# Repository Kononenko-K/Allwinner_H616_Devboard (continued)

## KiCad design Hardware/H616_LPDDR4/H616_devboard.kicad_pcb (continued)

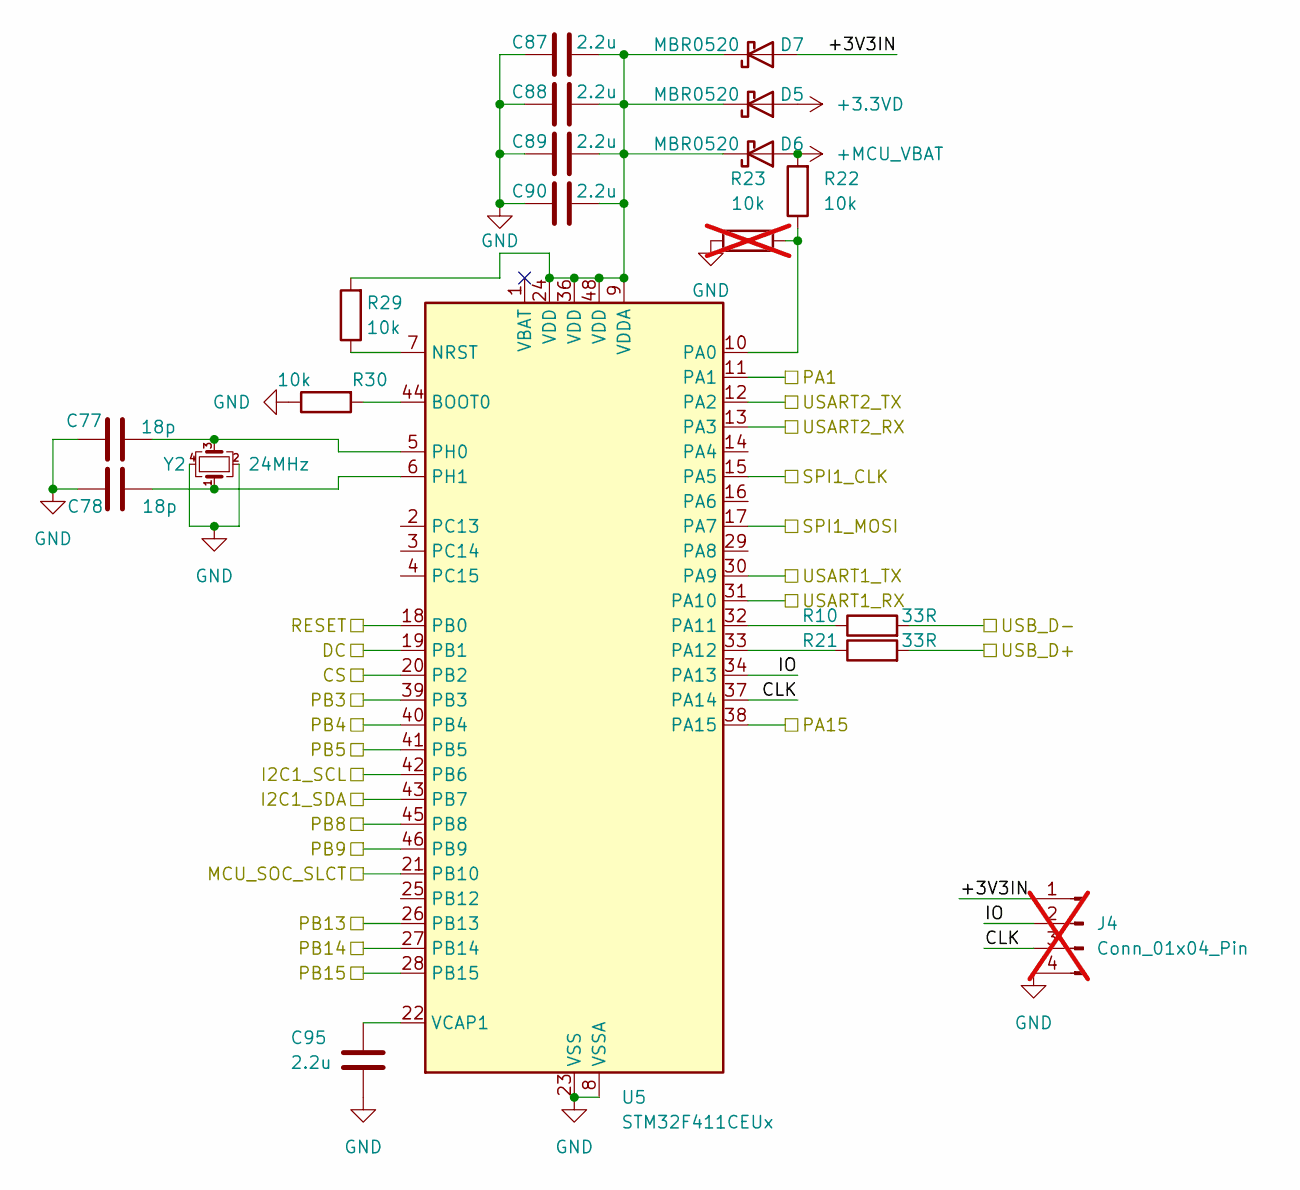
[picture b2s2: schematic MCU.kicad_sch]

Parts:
C77, C78: 18p; C_0402_1005Metric_Pad0.74x0.62mm_HandSolder; Part Number 0402CG180J500NT
C87, C88, C89, C90, C95: 2.2u; C_0402_1005Metric_Pad0.74x0.62mm_HandSolder; Part Number CL05A225KO5NQNC
D5, D6, D7: MBR0520; D_SOD-123; Part Number MBR0520
J4: Conn_01x04_Pin; PinHeader_1x04_P2.54mm_Vertical; not fitted
R10, R21: 33R; R_0402_1005Metric_Pad0.72x0.64mm_HandSolder; Part Number RC0402FR-0733RL
R22, R29, R30: 10k; R_0402_1005Metric_Pad0.72x0.64mm_HandSolder; Part Number RC0402FR-0710KL
R23: 10k; R_0402_1005Metric_Pad0.72x0.64mm_HandSolder; not fitted
U5: STM32F411CEUx; QFN-48-1EP_7x7mm_P0.5mm_EP5.6x5.6mm; Part Number STM32F411CEU6
Y2: 24MHz; Crystal_SMD_2520-4Pin_2.5x2.0mm; Part Number XTM25024000JT00351001

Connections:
+3.3VD: D5.2 (A); also elsewhere on the board
+MCU_VBAT: D6.2 (A), R22.2; also elsewhere on the board
/32R_SW: U5.28 (PB15); also elsewhere on the board
/AGC_SW: U5.27 (PB14); also elsewhere on the board
/CENTER_KEY: U5.40 (PB4); also elsewhere on the board
/IO1/DBG_RX2: U5.12 (PA2); also elsewhere on the board
/IO1/DBG_TX2: U5.13 (PA3); also elsewhere on the board
/IO1/UART5_RX: U5.30 (PA9); also elsewhere on the board
/IO1/UART5_TX: U5.31 (PA10); also elsewhere on the board
/LEFT_KEY: U5.39 (PB3); also elsewhere on the board
/MCU/+3V3IN: D7.2 (A), J4.1
/MCU/CLK: J4.3, U5.37 (PA14)
/MCU/CS: U5.20 (PB2); also elsewhere on the board
/MCU/DC: U5.19 (PB1); also elsewhere on the board
/MCU/I2C1_SCL: U5.42 (PB6); also elsewhere on the board
/MCU/I2C1_SDA: U5.43 (PB7); also elsewhere on the board
/MCU/IO: J4.2, U5.34 (PA13)
/MCU/MCU_SOC_SLCT: U5.21 (PB10); also elsewhere on the board
/MCU/PB8: U5.45 (PB8); also elsewhere on the board
/MCU/PB9: U5.46 (PB9); also elsewhere on the board
/MCU/RESET: U5.18 (PB0); also elsewhere on the board
/MCU/SPI1_CLK: U5.15 (PA5); also elsewhere on the board
/MCU/SPI1_MOSI: U5.17 (PA7); also elsewhere on the board
/MCU_D+: R21.2; also elsewhere on the board
/MCU_D-: R10.2; also elsewhere on the board
/N_CHRG: U5.11 (PA1); also elsewhere on the board
/POWER_KEY: U5.41 (PB5); also elsewhere on the board
/PSU_SW: U5.26 (PB13); also elsewhere on the board
/RIGHT_KEY: U5.38 (PA15); also elsewhere on the board
GND: C77.1, C78.1, C87.1, C88.1, C89.1, C90.1, C95.1, J4.4, R23.1, R30.1, U5.8 (VSSA), U5.23 (VSS), U5.35 (VSS), U5.47 (VSS), U5.49 (VSS), Y2.2, Y2.4; also elsewhere on the board
unnamed: C87.2, C88.2, C89.2, C90.2, D5.1 (K), D6.1 (K), D7.1 (K), R29.2, U5.9 (VDDA), U5.24 (VDD), U5.36 (VDD), U5.48 (VDD)
unnamed: R30.2, U5.44 (BOOT0)
unnamed: R29.1, U5.7 (NRST)
unnamed: R22.1, R23.2, U5.10 (PA0)
unnamed: R10.1, U5.32 (PA11)
unnamed: R21.1, U5.33 (PA12)
unnamed: C77.2, U5.5 (PH0), Y2.3
unnamed: C78.2, U5.6 (PH1), Y2.1
unnamed: C95.2, U5.22 (VCAP1)

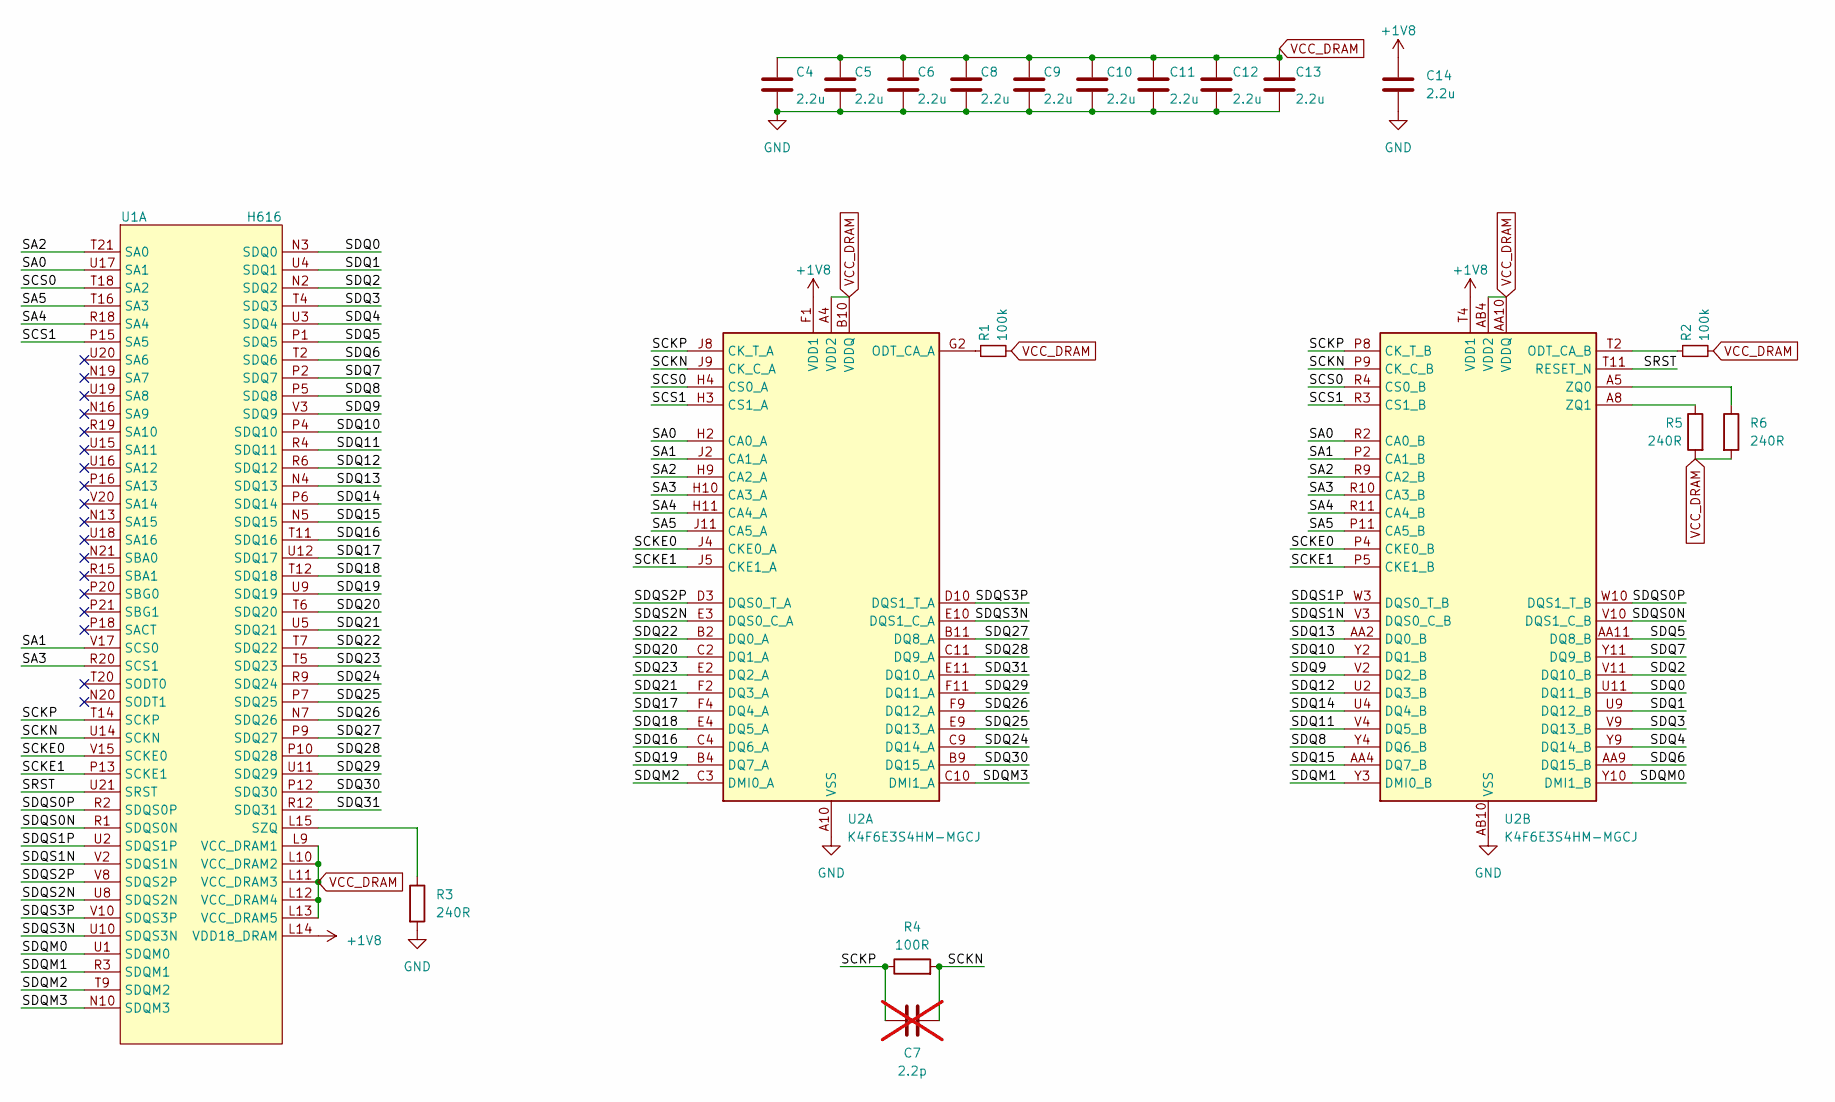
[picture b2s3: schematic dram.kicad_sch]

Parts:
C4, C5, C6, C8, C9, C10, C11, C12, C13, C14: 2.2u; C_0402_1005Metric_Pad0.74x0.62mm_HandSolder; Part Number CL05A225KO5NQNC
C7: 2.2p; C_0402_1005Metric_Pad0.74x0.62mm_HandSolder; not fitted
R1, R2: 100k; R_0402_1005Metric_Pad0.72x0.64mm_HandSolder; Part Number RC0402FR-07100KL
R3, R5, R6: 240R; R_0402_1005Metric_Pad0.72x0.64mm_HandSolder; Part Number RC0402FR-07240RL
R4: 100R; R_0402_1005Metric_Pad0.72x0.64mm_HandSolder; Part Number RC0402FR-07100RL
U1: H616; H616_TFBGA284; Part Number H616
U2: IS43LQ32256A-062BLI; BGA-200_10.0x14.5mm_Layout12x22_P0.80x0.65mm; Part Number K4F6E3S4HM-MGCJ

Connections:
+1V8: C14.1, U1.L14 (VDD18_DRAM), U2.F1 (VDD1), U2.F12 (VDD1), U2.G4 (VDD1), U2.G9 (VDD1), U2.T4 (VDD1), U2.T9 (VDD1), U2.U1 (VDD1), U2.U12 (VDD1); also elsewhere on the board
/DRAM/SA0: U1.U17 (SA1), U2.H2 (CA0_A), U2.R2 (CA0_B)
/DRAM/SA1: U1.V17 (SCS0), U2.J2 (CA1_A), U2.P2 (CA1_B)
/DRAM/SA2: U1.T21 (SA0), U2.H9 (CA2_A), U2.R9 (CA2_B)
/DRAM/SA3: U1.R20 (SCS1), U2.H10 (CA3_A), U2.R10 (CA3_B)
/DRAM/SA4: U1.R18 (SA4), U2.H11 (CA4_A), U2.R11 (CA4_B)
/DRAM/SA5: U1.T16 (SA3), U2.J11 (CA5_A), U2.P11 (CA5_B)
/DRAM/SCKE0: U1.V15 (SCKE0), U2.J4 (CKE0_A), U2.P4 (CKE0_B)
/DRAM/SCKE1: U1.P13 (SCKE1), U2.J5 (CKE1_A), U2.P5 (CKE1_B)
/DRAM/SCKN: C7.2, R4.2, U1.U14 (SCKN), U2.J9 (CK_C_A), U2.P9 (CK_C_B)
/DRAM/SCKP: C7.1, R4.1, U1.T14 (SCKP), U2.J8 (CK_T_A), U2.P8 (CK_T_B)
/DRAM/SCS0: U1.T18 (SA2), U2.H4 (CS0_A), U2.R4 (CS0_B)
/DRAM/SCS1: U1.P15 (SA5), U2.H3 (CS1_A), U2.R3 (CS1_B)
/DRAM/SDQ0: U1.N3 (SDQ0), U2.U11 (DQ11_B)
/DRAM/SDQ1: U1.U4 (SDQ1), U2.U9 (DQ12_B)
/DRAM/SDQ2: U1.N2 (SDQ2), U2.V11 (DQ10_B)
/DRAM/SDQ3: U1.T4 (SDQ3), U2.V9 (DQ13_B)
/DRAM/SDQ4: U1.U3 (SDQ4), U2.Y9 (DQ14_B)
/DRAM/SDQ5: U1.P1 (SDQ5), U2.AA11 (DQ8_B)
/DRAM/SDQ6: U1.T2 (SDQ6), U2.AA9 (DQ15_B)
/DRAM/SDQ7: U1.P2 (SDQ7), U2.Y11 (DQ9_B)
/DRAM/SDQ8: U1.P5 (SDQ8), U2.Y4 (DQ6_B)
/DRAM/SDQ9: U1.V3 (SDQ9), U2.V2 (DQ2_B)
/DRAM/SDQ10: U1.P4 (SDQ10), U2.Y2 (DQ1_B)
/DRAM/SDQ11: U1.R4 (SDQ11), U2.V4 (DQ5_B)
/DRAM/SDQ12: U1.R6 (SDQ12), U2.U2 (DQ3_B)
/DRAM/SDQ13: U1.N4 (SDQ13), U2.AA2 (DQ0_B)
/DRAM/SDQ14: U1.P6 (SDQ14), U2.U4 (DQ4_B)
/DRAM/SDQ15: U1.N5 (SDQ15), U2.AA4 (DQ7_B)
/DRAM/SDQ16: U1.T11 (SDQ16), U2.C4 (DQ6_A)
/DRAM/SDQ17: U1.U12 (SDQ17), U2.F4 (DQ4_A)
/DRAM/SDQ18: U1.T12 (SDQ18), U2.E4 (DQ5_A)
/DRAM/SDQ19: U1.U9 (SDQ19), U2.B4 (DQ7_A)
/DRAM/SDQ20: U1.T6 (SDQ20), U2.C2 (DQ1_A)
/DRAM/SDQ21: U1.U5 (SDQ21), U2.F2 (DQ3_A)
/DRAM/SDQ22: U1.T7 (SDQ22), U2.B2 (DQ0_A)
/DRAM/SDQ23: U1.T5 (SDQ23), U2.E2 (DQ2_A)
/DRAM/SDQ24: U1.R9 (SDQ24), U2.C9 (DQ14_A)
/DRAM/SDQ25: U1.P7 (SDQ25), U2.E9 (DQ13_A)
/DRAM/SDQ26: U1.N7 (SDQ26), U2.F9 (DQ12_A)
/DRAM/SDQ27: U1.P9 (SDQ27), U2.B11 (DQ8_A)
/DRAM/SDQ28: U1.P10 (SDQ28), U2.C11 (DQ9_A)
/DRAM/SDQ29: U1.U11 (SDQ29), U2.F11 (DQ11_A)
/DRAM/SDQ30: U1.P12 (SDQ30), U2.B9 (DQ15_A)
/DRAM/SDQ31: U1.R12 (SDQ31), U2.E11 (DQ10_A)
/DRAM/SDQM0: U1.U1 (SDQM0), U2.Y10 (DMI1_B)
/DRAM/SDQM1: U1.R3 (SDQM1), U2.Y3 (DMI0_B)
/DRAM/SDQM2: U1.T9 (SDQM2), U2.C3 (DMI0_A)
/DRAM/SDQM3: U1.N10 (SDQM3), U2.C10 (DMI1_A)
/DRAM/SDQS0N: U1.R1 (SDQS0N), U2.V10 (DQS1_C_B)
/DRAM/SDQS0P: U1.R2 (SDQS0P), U2.W10 (DQS1_T_B)
/DRAM/SDQS1N: U1.V2 (SDQS1N), U2.V3 (DQS0_C_B)
/DRAM/SDQS1P: U1.U2 (SDQS1P), U2.W3 (DQS0_T_B)
/DRAM/SDQS2N: U1.U8 (SDQS2N), U2.E3 (DQS0_C_A)
/DRAM/SDQS2P: U1.V8 (SDQS2P), U2.D3 (DQS0_T_A)
/DRAM/SDQS3N: U1.U10 (SDQS3N), U2.E10 (DQS1_C_A)
/DRAM/SDQS3P: U1.V10 (SDQS3P), U2.D10 (DQS1_T_A)
/DRAM/SRST: U1.U21 (SRST), U2.T11 (RESET_N)
GND: C4.2, C5.2, C6.2, C8.2, C9.2, C10.2, C11.2, C12.2, C13.2, C14.2, R3.2, U2.A3 (VSS), U2.A10 (VSS), U2.AB3 (VSS), U2.AB5 (VSS), U2.AB8 (VSS), U2.AB10 (VSS), U2.C1 (VSS), U2.C5 (VSS), U2.C8 (VSS), U2.C12 (VSS), U2.D2 (VSS), U2.D4 (VSS), U2.D9 (VSS), U2.D11 (VSS), U2.E1 (VSS), U2.E5 (VSS), U2.E8 (VSS), U2.E12 (VSS), U2.G1 (VSS), U2.G3 (VSS), U2.G5 (VSS), U2.G8 (VSS), U2.G10 (VSS), U2.G12 (VSS), U2.J1 (VSS), U2.J3 (VSS), U2.J10 (VSS), U2.J12 (VSS), U2.K2 (VSS), U2.K4 (VSS), U2.K9 (VSS), U2.K11 (VSS), U2.N2 (VSS), U2.N4 (VSS), U2.N9 (VSS), U2.N11 (VSS), U2.P1 (VSS), U2.P3 (VSS), U2.P10 (VSS), U2.P12 (VSS), U2.T1 (VSS), U2.T3 (VSS), U2.T5 (VSS), U2.T8 (VSS), U2.T10 (VSS), U2.T12 (VSS), U2.V1 (VSS), U2.V5 (VSS), U2.V8 (VSS), U2.V12 (VSS), U2.W2 (VSS), U2.W4 (VSS), U2.W9 (VSS), U2.W11 (VSS), U2.Y1 (VSS), U2.Y5 (VSS), U2.Y8 (VSS), U2.Y12 (VSS); also elsewhere on the board
unnamed: R3.1, U1.L15 (SZQ)
unnamed: R1.1, U2.G2 (ODT_CA_A)
unnamed: R2.1, U2.T2 (ODT_CA_B)
unnamed: R6.1, U2.A5 (ZQ0)
unnamed: R5.1, U2.A8 (ZQ1)
VCC_DRAM: C4.1, C5.1, C6.1, C8.1, C9.1, C10.1, C11.1, C12.1, C13.1, R1.2, R2.2, R5.2, R6.2, U1.L9 (VCC_DRAM1), U1.L10 (VCC_DRAM2), U1.L11 (VCC_DRAM3), U1.L12 (VCC_DRAM4), U1.L13 (VCC_DRAM5), U2.A4 (VDD2), U2.A9 (VDD2), U2.AA3 (VDDQ), U2.AA5 (VDDQ), U2.AA8 (VDDQ), U2.AA10 (VDDQ), U2.AB4 (VDD2), U2.AB9 (VDD2), U2.B3 (VDDQ), U2.B5 (VDDQ), U2.B8 (VDDQ), U2.B10 (VDDQ), U2.D1 (VDDQ), U2.D5 (VDDQ), U2.D8 (VDDQ), U2.D12 (VDDQ), U2.F3 (VDDQ), U2.F5 (VDD2), U2.F8 (VDD2), U2.F10 (VDDQ), U2.H1 (VDD2), U2.H5 (VDD2), U2.H8 (VDD2), U2.H12 (VDD2), U2.K1 (VDD2), U2.K3 (VDD2), U2.K10 (VDD2), U2.K12 (VDD2), U2.N1 (VDD2), U2.N3 (VDD2), U2.N10 (VDD2), U2.N12 (VDD2), U2.R1 (VDD2), U2.R5 (VDD2), U2.R8 (VDD2), U2.R12 (VDD2), U2.U3 (VDDQ), U2.U5 (VDD2), U2.U8 (VDD2), U2.U10 (VDDQ), U2.W1 (VDDQ), U2.W5 (VDDQ), U2.W8 (VDDQ), U2.W12 (VDDQ); also elsewhere on the board

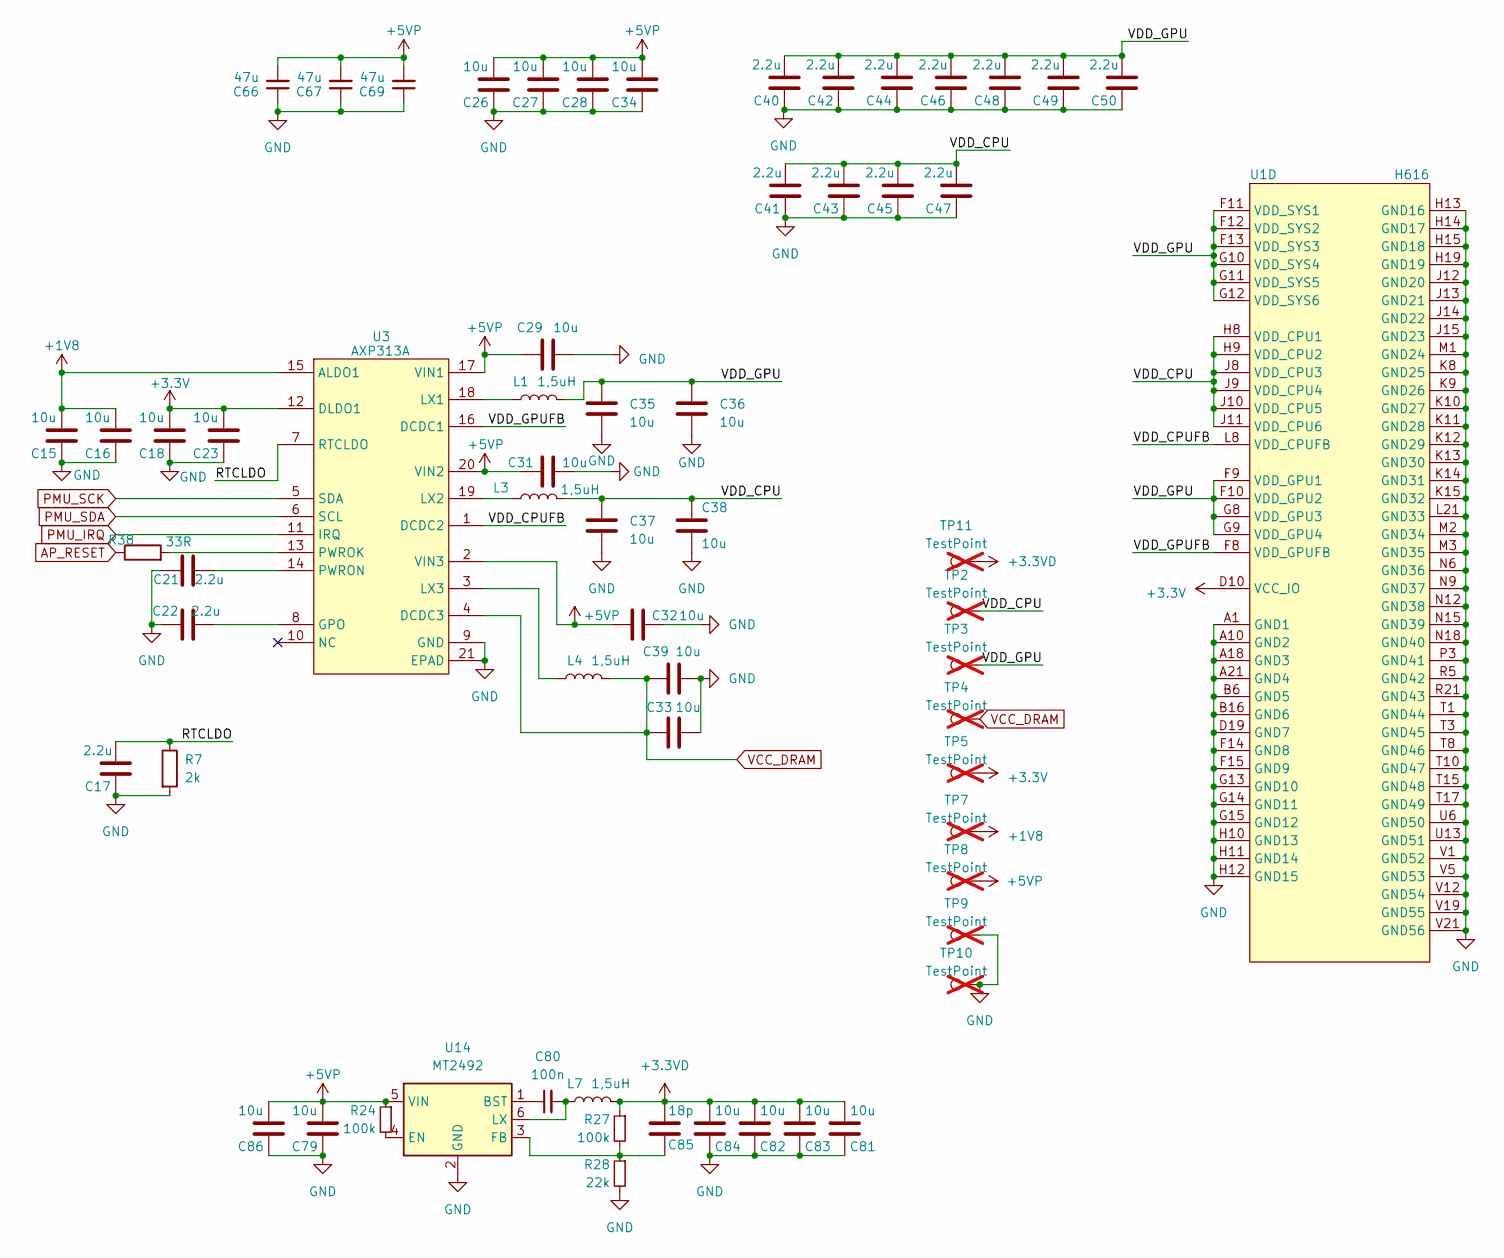
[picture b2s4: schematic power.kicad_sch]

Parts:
C15, C16, C18, C23, C26, C27, C28, C29, C31, C32, C33, C34, C35, C36, C37, C38, C39, C79, C81, C82, C83, C84, C86: 10u; C_0402_1005Metric_Pad0.74x0.62mm_HandSolder; Part Number GRM155R61A106ME44D
C17, C21, C22, C40, C41, C42, C43, C44, C45, C46, C47, C48, C49, C50: 2.2u; C_0402_1005Metric_Pad0.74x0.62mm_HandSolder; Part Number CL05A225KO5NQNC
C66, C67, C69: 47u; C_1210_3225Metric_Pad1.33x2.70mm_HandSolder; Part Number CS3225X7R476K160NRL
C80: 100n; C_0402_1005Metric_Pad0.74x0.62mm_HandSolder; Part Number CL05B104KO5NNNC
C85: 18p; C_0402_1005Metric_Pad0.74x0.62mm_HandSolder; Part Number 0402CG180J500NT
L1, L3, L4, L7: 1,5uH; L_Changjiang_FNR252010S; Part Number FTC252012S2R2MBCA
R7: 2k; R_0402_1005Metric_Pad0.72x0.64mm_HandSolder; Part Number RC0402FR-072KL
R24, R27: 100k; R_0402_1005Metric_Pad0.72x0.64mm_HandSolder; Part Number RC0402FR-07100KL
R28: 22k; R_0402_1005Metric_Pad0.72x0.64mm_HandSolder; Part Number RC0402FR-0722KL
R38: 33R; R_0402_1005Metric_Pad0.72x0.64mm_HandSolder; Part Number RC0402FR-0733RL
TP2, TP3, TP4, TP5, TP7, TP8, TP9, TP10, TP11: TestPoint; TestPoint_THTPad_D1.0mm_Drill0.5mm; not fitted
U1: H616; H616_TFBGA284; Part Number H616
U3: QFN-20-1EP_3x3mm_P0.4mm_EP1.65x1.65mm_ThermalVias; Part Number AXP313A
U14: MT2492; SOT-23-6; Part Number MT2492

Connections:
+1V8: C15.2, C16.2, TP7.1, U3.15 (ALDO1); also elsewhere on the board
+3.3V: C18.2, C23.2, TP5.1, U1.D10 (VCC_IO), U3.12 (DLDO1); also elsewhere on the board
+3.3VD: C81.2, C82.2, C83.2, C84.2, C85.2, L7.2, R27.1, TP11.1; also elsewhere on the board
+5VP: C26.2, C27.2, C28.2, C29.1, C31.1, C32.1, C34.2, C66.2, C67.2, C69.2, C79.2, C86.2, R24.1, TP8.1, U3.2 (VIN3), U3.17 (VIN1), U3.20 (VIN2), U14.5 (VIN); also elsewhere on the board
/POWER/RTCLDO: C17.2, R7.1, U3.7 (RTCLDO)
/POWER/VDD_CPU: C37.1, C38.2, C41.2, C43.2, C45.2, C47.2, L3.2, TP2.1, U1.H8 (VDD_CPU1), U1.H9 (VDD_CPU2), U1.J8 (VDD_CPU3), U1.J9 (VDD_CPU4), U1.J10 (VDD_CPU5), U1.J11 (VDD_CPU6)
/POWER/VDD_CPUFB: U1.L8 (VDD_CPUFB), U3.1 (DCDC2)
/POWER/VDD_GPU: C35.1, C36.1, C40.2, C42.2, C44.2, C46.2, C48.2, C49.2, C50.2, L1.2, TP3.1, U1.F9 (VDD_GPU1), U1.F10 (VDD_GPU2), U1.F11 (VDD_SYS1), U1.F12 (VDD_SYS2), U1.F13 (VDD_SYS3), U1.G8 (VDD_GPU3), U1.G9 (VDD_GPU4), U1.G10 (VDD_SYS4), U1.G11 (VDD_SYS5), U1.G12 (VDD_SYS6)
/POWER/VDD_GPUFB: U1.F8 (VDD_GPUFB), U3.16 (DCDC1)
AP_RESET: R38.1; also elsewhere on the board
GND: C15.1, C16.1, C17.1, C18.1, C21.1, C22.1, C23.1, C26.1, C27.1, C28.1, C29.2, C31.2, C32.2, C33.2, C34.1, C35.2, C36.2, C37.2, C38.1, C39.2, C40.1, C41.1, C42.1, C43.1, C44.1, C45.1, C46.1, C47.1, C48.1, C49.1, C50.1, C66.1, C67.1, C69.1, C79.1, C81.1, C82.1, C83.1, C84.1, C86.1, R7.2, R28.2, TP9.1, TP10.1, U1.A1 (GND1), U1.A10 (GND2), U1.A18 (GND3), U1.A21 (GND4), U1.B6 (GND5), U1.B16 (GND6), U1.D19 (GND7), U1.F14 (GND8), U1.F15 (GND9), U1.G13 (GND10), U1.G14 (GND11), U1.G15 (GND12), U1.H10 (GND13), U1.H11 (GND14), U1.H12 (GND15), U1.H13 (GND16), U1.H14 (GND17), U1.H15 (GND18), U1.H19 (GND19), U1.J12 (GND20), U1.J13 (GND21), U1.J14 (GND22), U1.J15 (GND23), U1.K8 (GND25), U1.K9 (GND26), U1.K10 (GND27), U1.K11 (GND28), U1.K12 (GND29), U1.K13 (GND30), U1.K14 (GND31), U1.K15 (GND32), U1.L21 (GND33), U1.M1 (GND24), U1.M2 (GND34), U1.M3 (GND35), U1.N6 (GND36), U1.N9 (GND37), U1.N12 (GND38), U1.N15 (GND39), U1.N18 (GND40), U1.P3 (GND41), U1.R5 (GND42), U1.R21 (GND43), U1.T1 (GND44), U1.T3 (GND45), U1.T8 (GND46), U1.T10 (GND47), U1.T15 (GND48), U1.T17 (GND49), U1.U6 (GND50), U1.U13 (GND51), U1.V1 (GND52), U1.V5 (GND53), U1.V12 (GND54), U1.V19 (GND55), U1.V21 (GND56), U3.9 (GND), U3.21 (EPAD), U14.2 (GND); also elsewhere on the board
unnamed: C22.2, U3.8 (GPO)
unnamed: L1.1, U3.18 (LX1)
unnamed: L3.1, U3.19 (LX2)
unnamed: L4.1, U3.3 (LX3)
unnamed: R38.2, U3.13 (PWROK)
unnamed: C21.2, U3.14 (PWRON)
unnamed: C80.1, U14.1 (BST)
unnamed: R24.2, U14.4 (EN)
unnamed: C85.1, R27.2, R28.1, U14.3 (FB)
unnamed: C80.2, L7.1, U14.6 (LX)
PMU_IRQ: U3.11 (IRQ); also elsewhere on the board
PMU_SCK: U3.5 (SDA); also elsewhere on the board
PMU_SDA: U3.6 (SCL); also elsewhere on the board
VCC_DRAM: C33.1, C39.1, L4.2, TP4.1, U3.4 (DCDC3); also elsewhere on the board

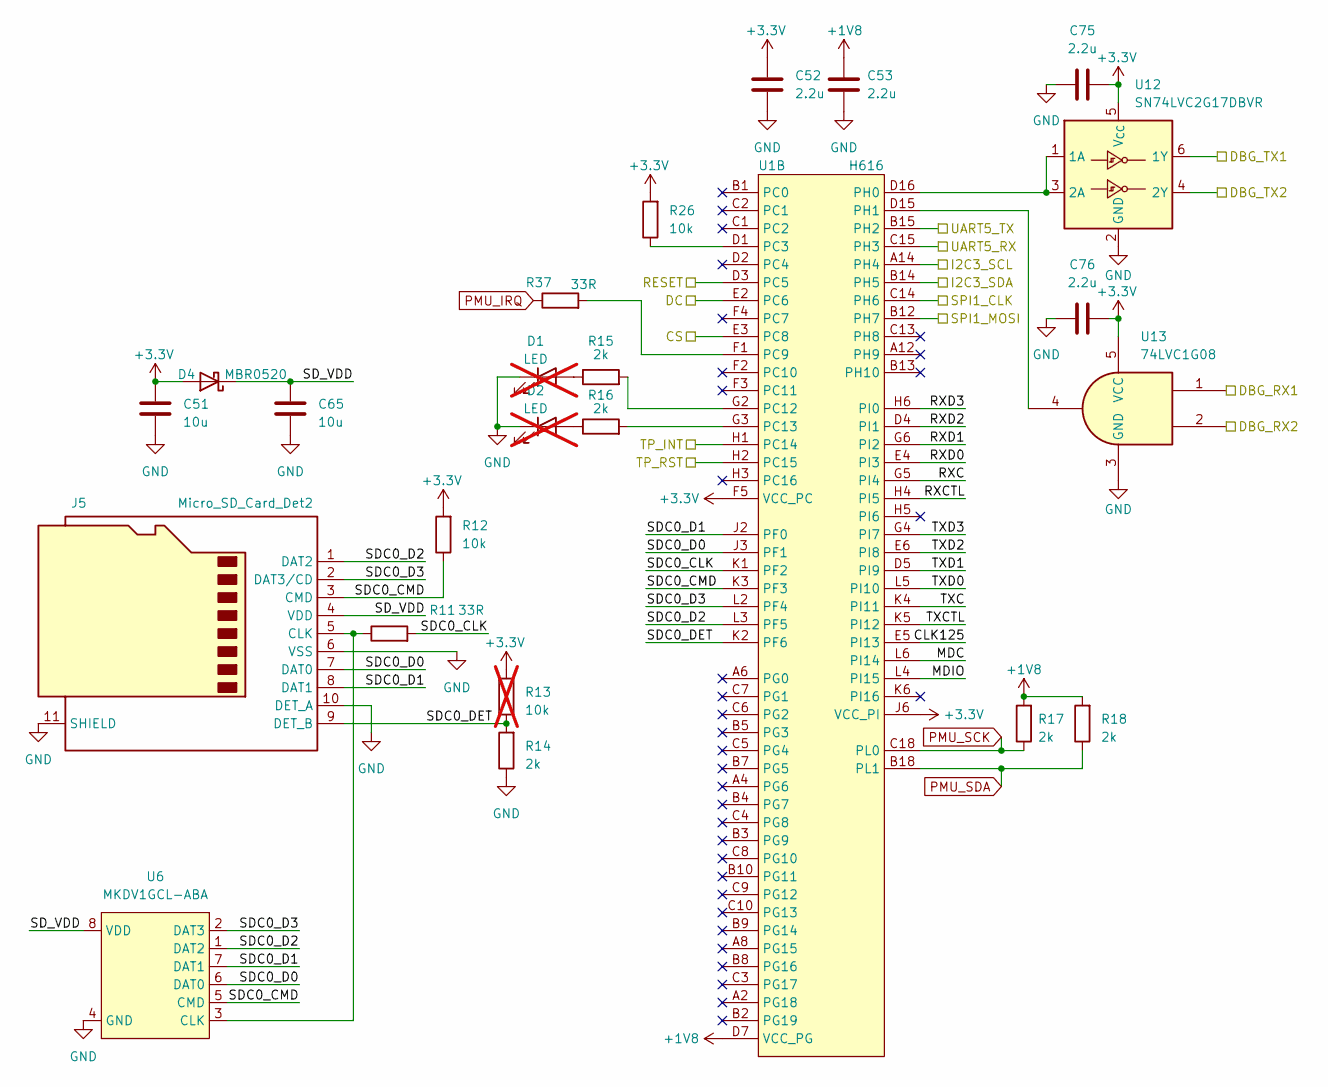
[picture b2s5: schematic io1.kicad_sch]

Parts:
C51, C65: 10u; C_0402_1005Metric_Pad0.74x0.62mm_HandSolder; Part Number GRM155R61A106ME44D
C52, C53, C75, C76: 2.2u; C_0402_1005Metric_Pad0.74x0.62mm_HandSolder; Part Number CL05A225KO5NQNC
D1, D2: LED; LED_0603_1608Metric_Pad1.05x0.95mm_HandSolder; not fitted
D4: MBR0520; D_SOD-123; Part Number MBR0520
J5: Micro_SD_Card_Det2; microSD_HC_Hirose_DM3AT-SF-PEJM5; Part Number HRS(Hirose)
R11, R37: 33R; R_0402_1005Metric_Pad0.72x0.64mm_HandSolder; Part Number RC0402FR-0733RL
R12, R26: 10k; R_0402_1005Metric_Pad0.72x0.64mm_HandSolder; Part Number RC0402FR-0710KL
R13: 10k; R_0402_1005Metric_Pad0.72x0.64mm_HandSolder; not fitted
R14, R15, R16, R17, R18: 2k; R_0402_1005Metric_Pad0.72x0.64mm_HandSolder; Part Number RC0402FR-072KL
U1: H616; H616_TFBGA284; Part Number H616
U6: MKDV1GCL-ABA; LGA-8_8x6mm_P1.27mm; Part Number MKDV08GCL-STP
U12: SN74LVC2G17DBVR; SOT-23-6; Part Number SN74LVC2G17DBVR(UMW)
U13: 74LVC1G08; SOT-23-5; Part Number 74LVC1G08GV

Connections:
+1V8: C53.1, R17.2, R18.2, U1.D7 (VCC_PG); also elsewhere on the board
+3.3V: C51.1, C52.1, C75.2, C76.2, D4.2 (A), R12.2, R13.2, R26.2, U1.F5 (VCC_PC), U1.J6 (VCC_PI), U12.5 (V_{CC}), U13.5 (VCC); also elsewhere on the board
/IO1/CLK125: U1.E5 (PI13)
/IO1/CS: U1.E3 (PC8); also elsewhere on the board
/IO1/DBG_RX1: U13.1; also elsewhere on the board
/IO1/DBG_RX2: U13.2; also elsewhere on the board
/IO1/DBG_TX1: U12.6 (1Y); also elsewhere on the board
/IO1/DBG_TX2: U12.4 (2Y); also elsewhere on the board
/IO1/DC: U1.E2 (PC6); also elsewhere on the board
/IO1/MDC: U1.L6 (PI14)
/IO1/MDIO: U1.L4 (PI15)
/IO1/RESET: U1.D3 (PC5); also elsewhere on the board
/IO1/RXC: U1.G5 (PI4)
/IO1/RXCTL: U1.H4 (PI5)
/IO1/RXD0: U1.E4 (PI3)
/IO1/RXD1: U1.G6 (PI2)
/IO1/RXD2: U1.D4 (PI1)
/IO1/RXD3: U1.H6 (PI0)
/IO1/SDC0_CLK: R11.2, U1.K1 (PF2)
/IO1/SDC0_CMD: J5.3 (CMD), R12.1, U1.K3 (PF3), U6.5 (CMD)
/IO1/SDC0_D0: J5.7 (DAT0), U1.J3 (PF1), U6.6 (DAT0)
/IO1/SDC0_D1: J5.8 (DAT1), U1.J2 (PF0), U6.7 (DAT1)
/IO1/SDC0_D2: J5.1 (DAT2), U1.L3 (PF5), U6.1 (DAT2)
/IO1/SDC0_D3: J5.2 (DAT3/CD), U1.L2 (PF4), U6.2 (DAT3)
/IO1/SDC0_DET: J5.9 (DET_B), R13.1, R14.2, U1.K2 (PF6)
/IO1/SD_VDD: C65.1, D4.1 (K), J5.4 (VDD), U6.8 (VDD)
/IO1/SPI1_CLK: U1.C14 (PH6); also elsewhere on the board
/IO1/SPI1_MOSI: U1.B12 (PH7); also elsewhere on the board
/IO1/TXC: U1.K4 (PI11)
/IO1/TXCTL: U1.K5 (PI12)
/IO1/TXD0: U1.L5 (PI10)
/IO1/TXD1: U1.D5 (PI9)
/IO1/TXD2: U1.E6 (PI8)
/IO1/TXD3: U1.G4 (PI7)
/IO1/UART5_RX: U1.C15 (PH3); also elsewhere on the board
/IO1/UART5_TX: U1.B15 (PH2); also elsewhere on the board
/TP_INT: U1.H1 (PC14); also elsewhere on the board
/TP_RST: U1.H2 (PC15); also elsewhere on the board
/TP_SCL: U1.A14 (PH4); also elsewhere on the board
/TP_SDA: U1.B14 (PH5); also elsewhere on the board
GND: C51.2, C52.2, C53.2, C65.2, C75.1, C76.1, D1.1 (K), D2.1 (K), J5.6 (VSS), J5.10 (DET_A), J5.11 (SHIELD), R14.1, U6.4 (GND), U12.2 (GND), U13.3 (GND); also elsewhere on the board
unnamed: D1.2 (A), R15.1
unnamed: D2.2 (A), R16.1
unnamed: J5.5 (CLK), R11.1, U6.3 (CLK)
unnamed: R26.1, U1.D1 (PC3)
unnamed: R37.2, U1.F1 (PC9)
unnamed: R15.2, U1.G2 (PC12)
unnamed: R16.2, U1.G3 (PC13)
unnamed: U1.D15 (PH1), U13.4
unnamed: U1.D16 (PH0), U12.1 (1A), U12.3 (2A)
PMU_IRQ: R37.1; also elsewhere on the board
PMU_SCK: R17.1, U1.C18 (PL0); also elsewhere on the board
PMU_SDA: R18.1, U1.B18 (PL1); also elsewhere on the board

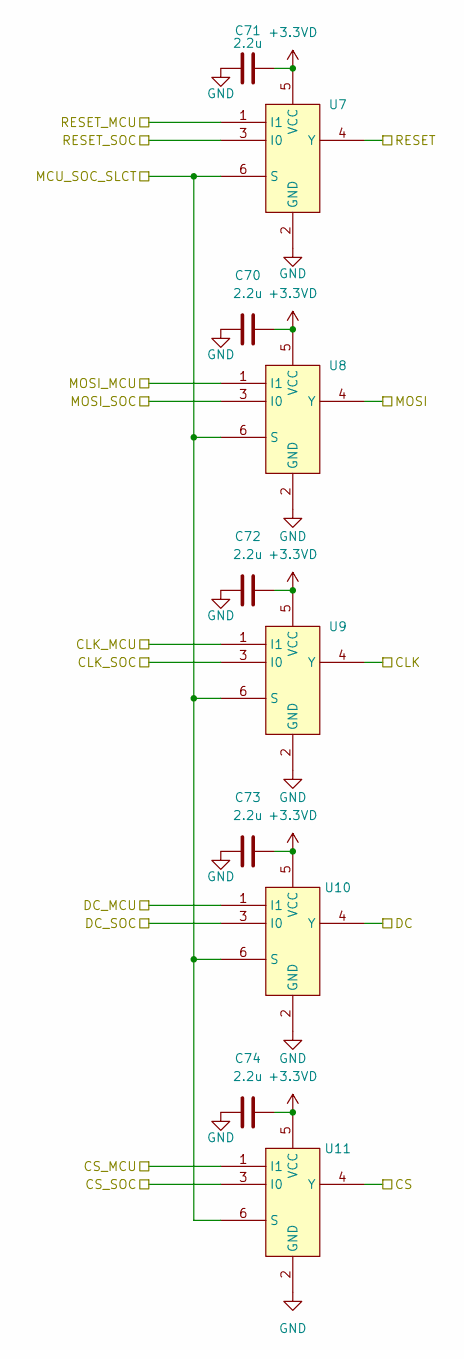
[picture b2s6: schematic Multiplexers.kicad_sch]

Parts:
C70, C71, C72, C73, C74: 2.2u; C_0402_1005Metric_Pad0.74x0.62mm_HandSolder; Part Number CL05A225KO5NQNC
U7, U8, U9, U10, U11: SOT-23-6; Part Number SN74LVC1G157DB(LX)

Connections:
+3.3VD: C70.2, C71.2, C72.2, C73.2, C74.2, U7.5 (VCC), U8.5 (VCC), U9.5 (VCC), U10.5 (VCC), U11.5 (VCC); also elsewhere on the board
/CLK: U9.4 (Y); also elsewhere on the board
/CS: U11.4 (Y); also elsewhere on the board
/DC: U10.4 (Y); also elsewhere on the board
/IO1/CS: U11.3 (I0); also elsewhere on the board
/IO1/DC: U10.3 (I0); also elsewhere on the board
/IO1/RESET: U7.3 (I0); also elsewhere on the board
/IO1/SPI1_CLK: U9.3 (I0); also elsewhere on the board
/IO1/SPI1_MOSI: U8.3 (I0); also elsewhere on the board
/MCU/CS: U11.1 (I1); also elsewhere on the board
/MCU/DC: U10.1 (I1); also elsewhere on the board
/MCU/MCU_SOC_SLCT: U7.6 (S), U8.6 (S), U9.6 (S), U10.6 (S), U11.6 (S); also elsewhere on the board
/MCU/RESET: U7.1 (I1); also elsewhere on the board
/MCU/SPI1_CLK: U9.1 (I1); also elsewhere on the board
/MCU/SPI1_MOSI: U8.1 (I1); also elsewhere on the board
/MOSI: U8.4 (Y); also elsewhere on the board
/RESET: U7.4 (Y); also elsewhere on the board
GND: C70.1, C71.1, C72.1, C73.1, C74.1, U7.2 (GND), U8.2 (GND), U9.2 (GND), U10.2 (GND), U11.2 (GND); also elsewhere on the board

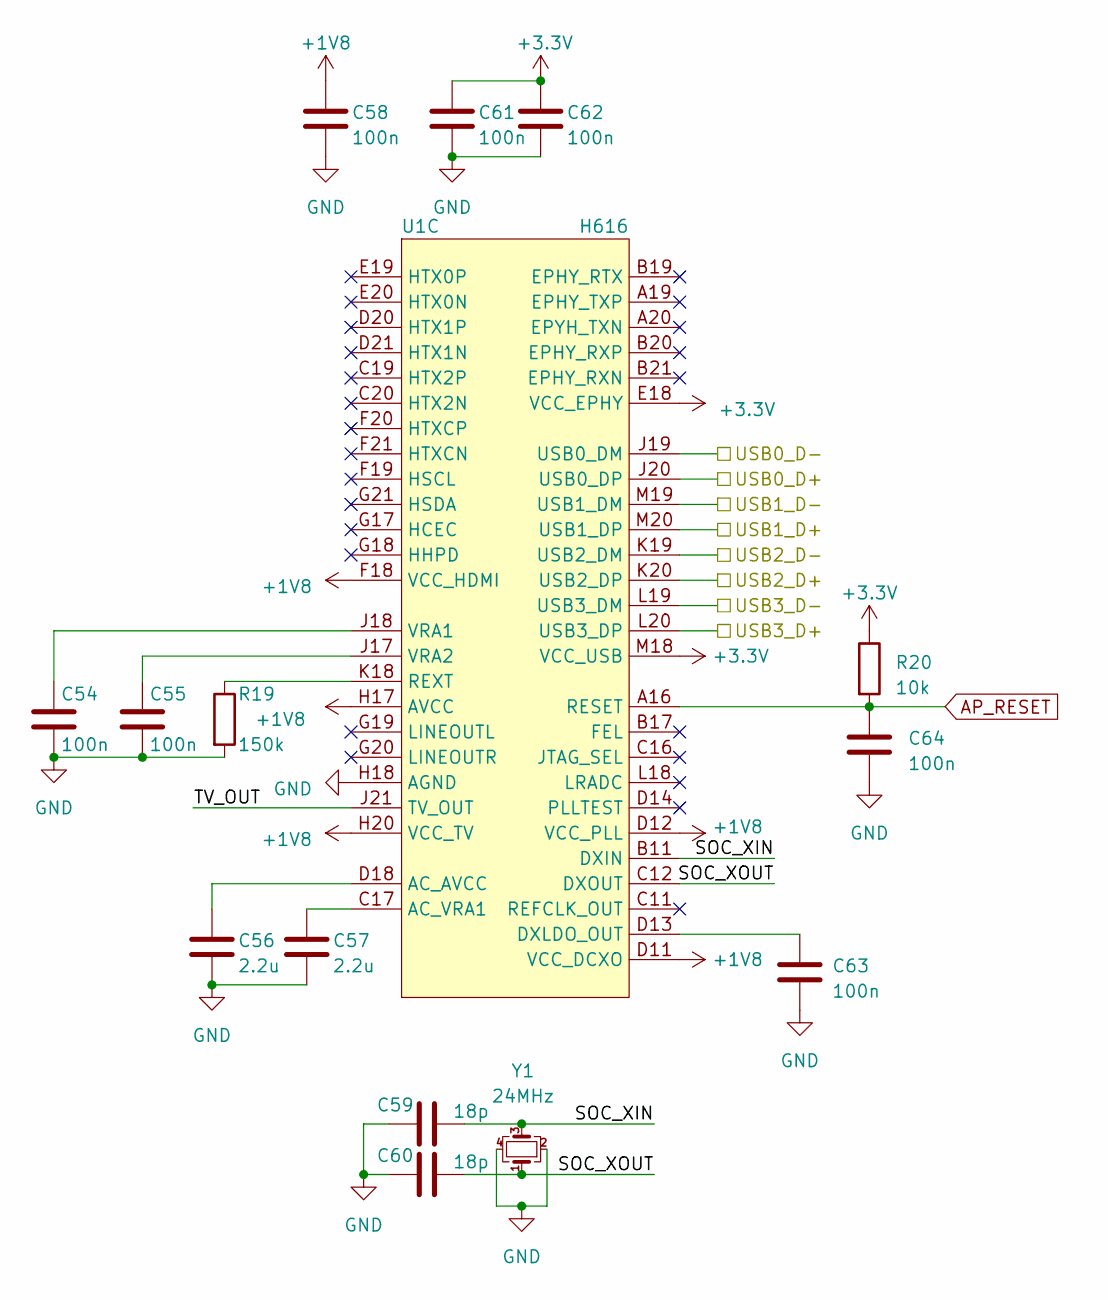
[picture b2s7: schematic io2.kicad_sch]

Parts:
C54, C55, C58, C61, C62, C63, C64: 100n; C_0402_1005Metric_Pad0.74x0.62mm_HandSolder; Part Number CL05B104KO5NNNC
C56, C57: 2.2u; C_0402_1005Metric_Pad0.74x0.62mm_HandSolder; Part Number CL05A225KO5NQNC
C59, C60: 18p; C_0402_1005Metric_Pad0.74x0.62mm_HandSolder; Part Number 0402CG180J500NT
R19: 150k; R_0402_1005Metric_Pad0.72x0.64mm_HandSolder; Part Number RC0402FR-07150KL
R20: 10k; R_0402_1005Metric_Pad0.72x0.64mm_HandSolder; Part Number RC0402FR-0710KL
U1: H616; H616_TFBGA284; Part Number H616
Y1: 24MHz; Crystal_SMD_2520-4Pin_2.5x2.0mm; Part Number XTM25024000JT00351001

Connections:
+1V8: C58.1, U1.D11 (VCC_DCXO), U1.D12 (VCC_PLL), U1.F18 (VCC_HDMI), U1.H17 (AVCC), U1.H20 (VCC_TV); also elsewhere on the board
+3.3V: C61.1, C62.1, R20.1, U1.E18 (VCC_EPHY), U1.M18 (VCC_USB); also elsewhere on the board
/AUX_D+: U1.J20 (USB0_DP); also elsewhere on the board
/AUX_D-: U1.J19 (USB0_DM); also elsewhere on the board
/CODEC_D+: U1.K20 (USB2_DP); also elsewhere on the board
/CODEC_D-: U1.K19 (USB2_DM); also elsewhere on the board
/IO2/SOC_XIN: C59.2, U1.B11 (DXIN), Y1.3
/IO2/SOC_XOUT: C60.2, U1.C12 (DXOUT), Y1.1
/IO2/TV_OUT: U1.J21 (TV_OUT)
/IO2/USB3_D+: U1.L20 (USB3_DP)
/IO2/USB3_D-: U1.L19 (USB3_DM)
/MCU_D+: U1.M20 (USB1_DP); also elsewhere on the board
/MCU_D-: U1.M19 (USB1_DM); also elsewhere on the board
AP_RESET: C64.1, R20.2, U1.A16 (RESET); also elsewhere on the board
GND: C54.2, C55.2, C56.2, C57.2, C58.2, C59.1, C60.1, C61.2, C62.2, C63.2, C64.2, R19.2, U1.H18 (AGND), Y1.2, Y1.4; also elsewhere on the board
unnamed: C56.1, U1.D18 (AC_AVCC)
unnamed: C57.1, U1.C17 (AC_VRA1)
unnamed: C63.1, U1.D13 (DXLDO_OUT)
unnamed: R19.1, U1.K18 (REXT)
unnamed: C54.1, U1.J18 (VRA1)
unnamed: C55.1, U1.J17 (VRA2)

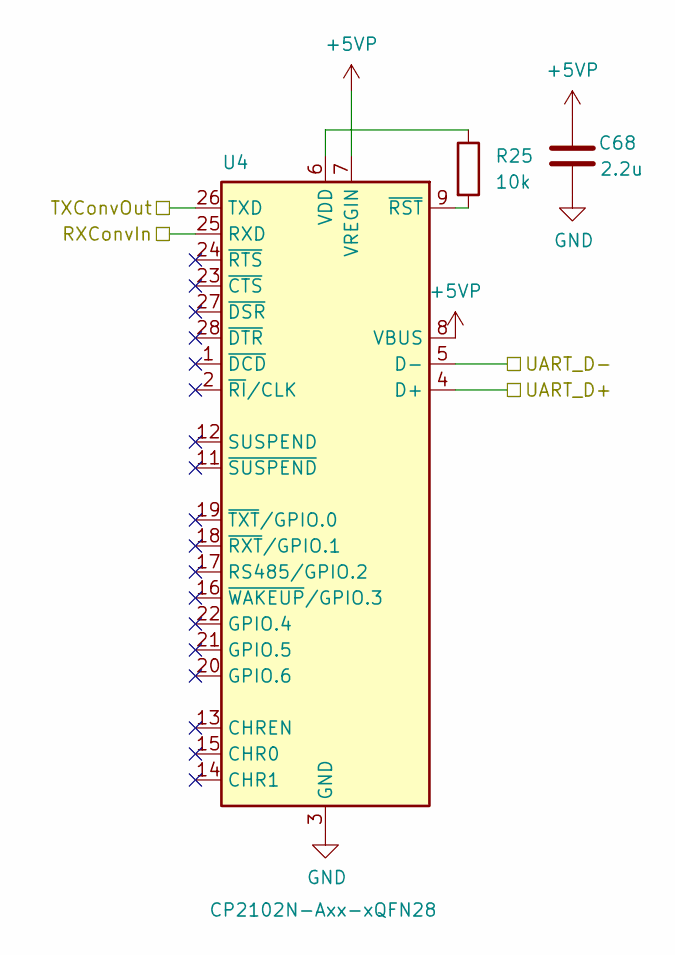
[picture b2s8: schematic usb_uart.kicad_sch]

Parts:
C68: 2.2u; C_0402_1005Metric_Pad0.74x0.62mm_HandSolder; Part Number CL05A225KO5NQNC
R25: 10k; R_0402_1005Metric_Pad0.72x0.64mm_HandSolder; Part Number RC0402FR-0710KL
U4: CP2102N-Axx-xQFN28; QFN-28-1EP_5x5mm_P0.5mm_EP3.35x3.35mm; Part Number CP2102-GMR

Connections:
+5VP: C68.1, U4.7 (VREGIN), U4.8 (VBUS); also elsewhere on the board
/DBG_D+: U4.4 (D+); also elsewhere on the board
/DBG_D-: U4.5 (D-); also elsewhere on the board
/IO1/DBG_RX1: U4.26 (TXD); also elsewhere on the board
/IO1/DBG_TX1: U4.25 (RXD); also elsewhere on the board
GND: C68.2, U4.3 (GND), U4.29 (GND); also elsewhere on the board
unnamed: R25.1, U4.6 (VDD)
unnamed: R25.2, U4.9 (~RST)

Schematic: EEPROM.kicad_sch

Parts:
C94: 2.2u; C_0402_1005Metric_Pad0.74x0.62mm_HandSolder; Part Number CL05A225KO5NQNC
D3: MBR0520; D_SOD-123; Part Number MBR0520
R31, R32: 10k; R_0402_1005Metric_Pad0.72x0.64mm_HandSolder; Part Number RC0402FR-0710KL
U17: M24C02-FMN; SOIC-8_3.9x4.9mm_P1.27mm; Part Number M24C02-WMN6TP

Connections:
+3.3V: D3.2 (A); also elsewhere on the board
/TP_SCL: R32.1, U17.6 (SCL); also elsewhere on the board
/TP_SDA: R31.1, U17.5 (SDA); also elsewhere on the board
GND: C94.1, U17.1 (E0), U17.2 (E1), U17.3 (E2), U17.4 (VSS), U17.7 (~WC); also elsewhere on the board
unnamed: C94.2, D3.1 (K), R31.2, R32.2, U17.8 (VCC)
